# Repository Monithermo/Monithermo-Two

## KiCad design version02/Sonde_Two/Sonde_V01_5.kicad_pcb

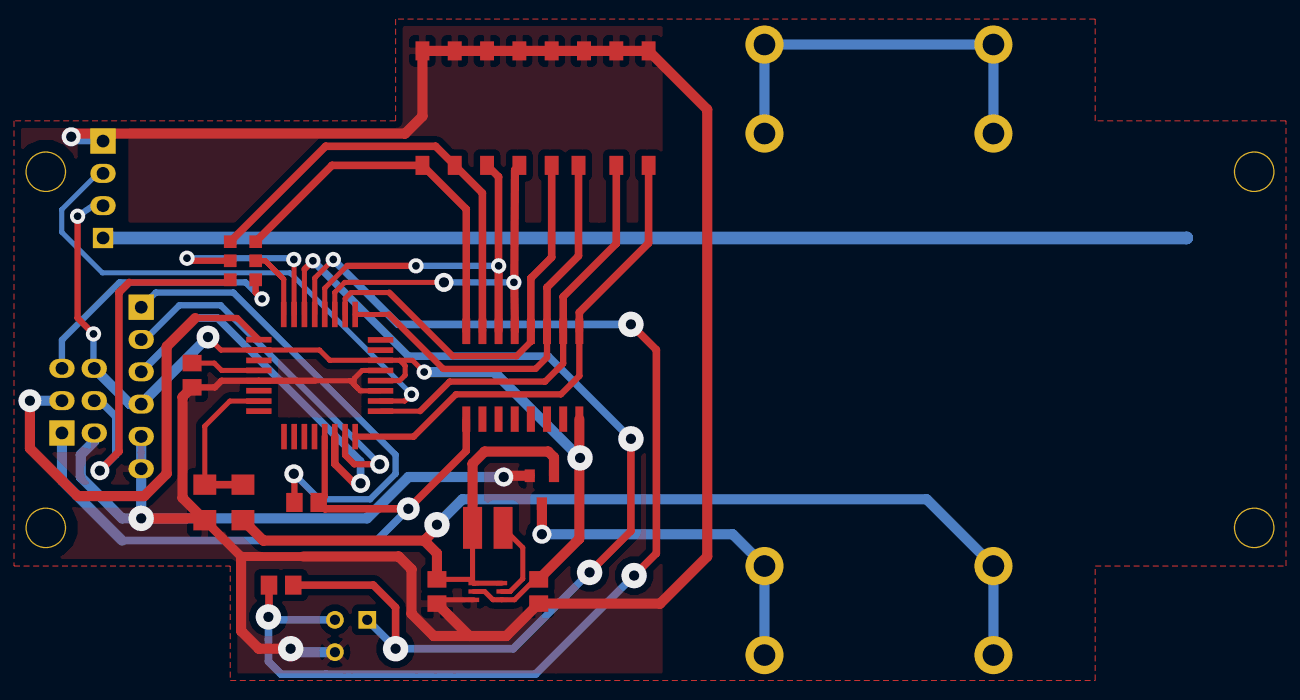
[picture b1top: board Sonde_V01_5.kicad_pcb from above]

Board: 2 copper layers, 29 parts (0 on the bottom side), 29 nets.

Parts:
BT1, BT2: Pile AA; pile_AA_remanie
C1, C2: 4.7uF; c_0805
C3, C4: 100nF; c_0805
IC1: ATMEGA328P-A; TQFP32
L1: 4.7uH; Bobine
P1: ISP; SIL-3x2
P2: Prog; SIL-6
P3: Antenne_PCB; Ant
P4: Percage 4; vis-3.2mm
P5: percage 3; vis-3.2mm
P6: percage 2; vis-3.2mm
P7: Percage 1; vis-3.2mm
Q1: BSS138; SOT23
R1: 820k; c_1206
R2: 330k; c_1206
R3: 4.7k; c_0805
RP1: 1M; SOM16
SW1: PRG1; switch_pad
SW2: PRG2; switch_pad
Sym1: BIG_SYMBOL_CREATIVECOMMONS_TYP2; Symbol_CreativeCommons_SilkscreenTop_Type2_Small
Sym2: BIG_SYMBOL_CC-SHAREALIKE; Symbol_CC-ShareAlike_SilkscreenTop_Small
Sym3: BIG_SYMBOL_CC-NONCOMMERCIAL; Symbol_CC-Noncommercial_SilkscreenTop_Small
TX1: QAM-TX1-433; SIL-4
U1: TPS61222; DCK
U2: DS18B20; TO92
U3: Switch ID; DIP_16_CMS

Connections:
+3.3V: C2.1, IC1.4, IC1.6, IC1.18, P1.4, P2.4, RP1.16, TX1.3, U1.2, U1.4
+BATT: BT1.1, C1.1, L1.1, Q1.1, R1.1, U1.1, U1.6
/Ant: P3.1, TX1.4
/D2: IC1.32, RP1.1, U3.16
/D3: IC1.1, RP1.2, U3.15
/D5: IC1.9, RP1.3, U3.14
/D6: IC1.10, RP1.4, U3.13
/D7: IC1.11, RP1.5, U3.12
/D8: IC1.12, RP1.6, U3.11
/D11: RP1.7, SW1.3, U3.10
/D12: RP1.8, SW2.3, U3.9
/MISO: P1.3, SW2.1
/MOSI: P1.5, SW1.1
/PB3: IC1.15, SW1.2
/PB4: IC1.16, SW2.2
/RX: IC1.30, P2.3
/Reset: C3.2, IC1.29, P1.1, RP1.9
/SCK: IC1.17, P1.2
/TX: IC1.31, P2.2
/Ubat: IC1.23, R1.2, R2.1
/data: IC1.2, TX1.2
GND: C1.2, C2.2, C4.2, IC1.3, IC1.5, IC1.21, P1.6, P2.5, P2.6, Q1.2, R2.2, TX1.1, U1.3, U2.3, U3.1, U3.2, U3.3, U3.4, U3.5, U3.6, U3.7, U3.8
GNDPWR: BT2.2, Q1.3
unnamed: C4.1, IC1.20
unnamed: C3.1, P2.1
unnamed: L1.2, U1.5
unnamed: IC1.14, R3.2, U2.1
unnamed: IC1.13, R3.1, U2.2
unnamed: BT1.2, BT2.1

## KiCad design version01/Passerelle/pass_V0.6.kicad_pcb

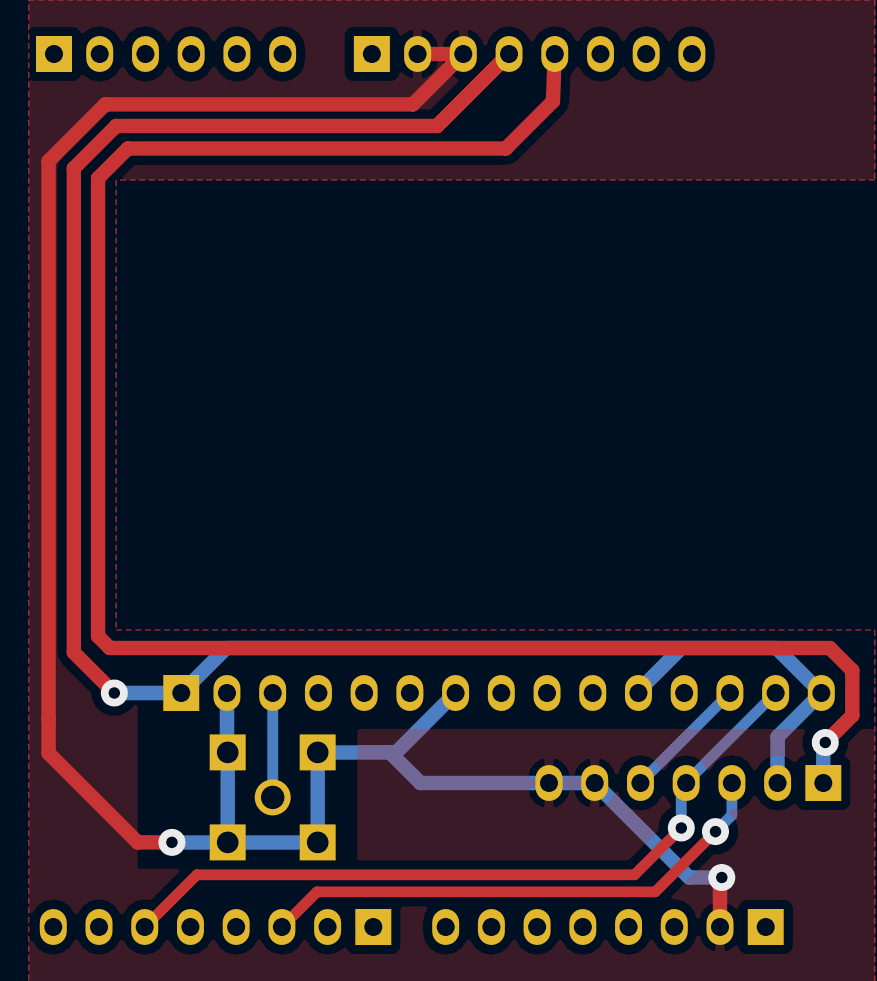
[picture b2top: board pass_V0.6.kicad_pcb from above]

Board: 2 copper layers, 10 parts (0 on the bottom side), 7 nets.

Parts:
A1: ANTENNA; SMA
P1: CONN_7; SIL-7
P2: CONN_6; SIL-6
P3, P5, P6: CONN_8; SIL-8
P4: Recepteur; SIL-15
Sym1: BIG_SYMBOL_CREATIVECOMMONS_TYP2; Symbol_CreativeCommons_SilkscreenTop_Type2_Small
Sym2: BIG_SYMBOL_CC-SHAREALIKE; Symbol_CC-ShareAlike_SilkscreenTop_Small
Sym3: BIG_SYMBOL_CC-NONCOMMERCIAL; Symbol_CC-Noncommercial_SilkscreenTop_Small

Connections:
/3.3V: P1.1, P5.5
/5V: P1.2, P4.1, P4.11, P4.15, P5.4
/Ant: A1.1, P4.3
/GND: A1.2, A1.3, A1.4, A1.5, P1.6, P1.7, P4.2, P4.7, P5.2, P5.3, P6.2
/RSSI: P1.5, P4.13
/RX: P1.3, P3.3
/data: P1.4, P3.6, P4.14

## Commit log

2016-06-15 first release
